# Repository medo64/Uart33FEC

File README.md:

[UART 3.3V Framework Expansion Card](https://medo64.com/uart33fec/)
===================================================================

This Framework laptop expansion card will show up on your system as a serial
device and allow for a non-isolated serial UART communication up to 1 Mbaud
baud rate.

Please note that this card is not using RS-232 but 3.3V TTL.

## UART Pinout

To connect to this board, one has to use a 4-pin JST XH connector. The following
table represents the pinout, pin 1 being on the left as looking into the
expansion card.

| # | Ref | Description                     |
|--:|:---:|---------------------------------|
| 2 | GND | Ground connection               |
| 1 | RXD | Receive (3.3V TTL)              |
| 3 | TXD | Transmit (3.3V TTL)             |
| 4 | 3V3 | 3.3V 400mA (typical) output     |

Using 22 AWG wire 0.25 mm² is recommended.

## Supported Speeds

This board employs the FT232R as its UART chip, and consequently, it supports
all the baud rates this chip [can handle](https://ftdichip.com/Documents/AppNotes/AN232B-05_BaudRates.pdf).
The table below lists the standard baud rates.

| Baud rate |    Actual | Error |    Divisor |
|----------:|----------:|------:|-----------:|
|       300 |       300 | 0.00% |  10000.000 |
|       600 |       600 | 0.00% |   5000.000 |
|     1,200 |     1,200 | 0.00% |   2500.000 |
|     1,800 |     1,800 | 0.00% |   1666.625 |
|     2,400 |     2,400 | 0.00% |   1250.000 |
|     4,800 |     4,800 | 0.00% |    625.000 |
|     7,200 |     7,201 | 0.01% |    416.625 |
|     9,600 |     9,600 | 0.00% |    312.500 |
|    14,400 |    14,406 | 0.04% |    208.250 |
|    19,200 |    19,200 | 0.00% |    156.250 |
|    28,800 |    28,812 | 0.04% |    104.125 |
|    38,400 |    38,400 | 0.00% |     78.125 |
|    57,600 |    57,692 | 0.16% |     52.000 |
|   115,200 |   115,385 | 0.16% |     26.000 |
|   230,400 |   230,769 | 0.16% |     13.000 |
|   460,800 |   461,538 | 0.16% |      6.500 |
|   921,600 |   923,077 | 0.16% |      3.250 |
| 1,000,000 | 1,000,000 | 0.00% |      3.000 |

While chip does support baud rates up to 3 Mbaud, granularity of such rates
is severely limited.

---
*You can check my blog and other projects at [www.medo64.com](https://www.medo64.com/electronics/).*

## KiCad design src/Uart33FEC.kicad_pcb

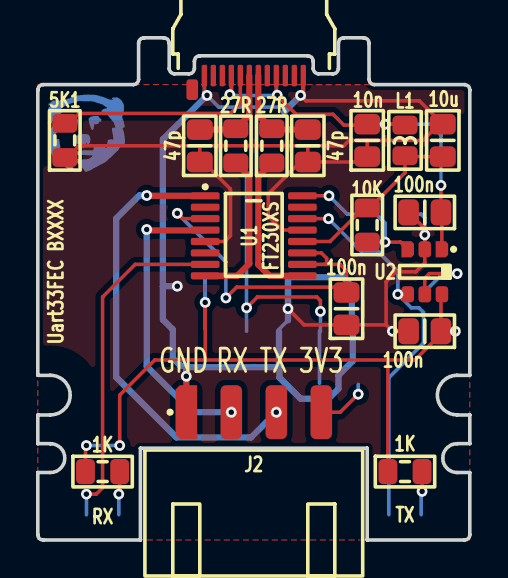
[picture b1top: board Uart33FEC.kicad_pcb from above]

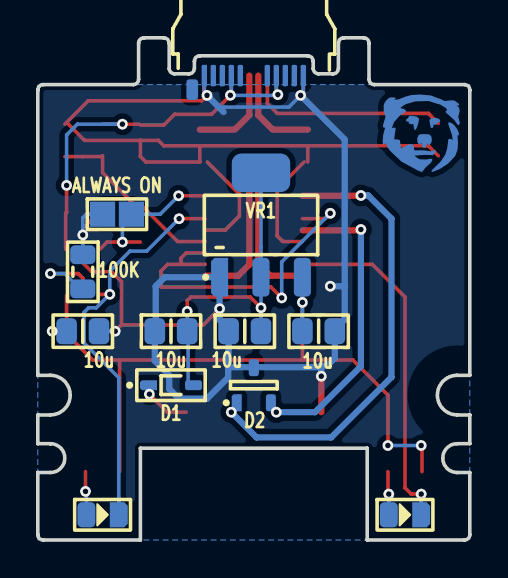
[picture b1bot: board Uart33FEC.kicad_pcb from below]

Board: 2 copper layers, 24.0 x 27.9 mm, 30 parts (12 on the bottom side), 20 nets.

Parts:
C1, C2: 47p; C (0805)
C3: 10n; C (0805)
C4, C5, C6: 100n; C (0805)
C7, C8, C9, C10, C11: 10u; C (0805)
D1: CUS08F30; D (SOD323)
D2: SM05T1G; D TVS 3.3V [D1213A-02SOL-7] (SOT23-3)
DS1: RX; DS (0805)
DS2: TX; DS (0805)
ICON: Medo64; ICON Medo64
J1: 105444-0001; J USB C 3.2 Edge (24w)
J2: B4B-XH-A; J JST XH Edge [UART] (4w)
JP1: ALWAYS ON; JP (0805)
L1: 600R; L (0805)
R1, R2: 27R; R (0805)
R3, R4: 1K; R (0805)
R5: 5K1; R (0805)
R6: 10K; R (0805)
R7: 100K; R (0805)
U1: FT230XS; U Transceiver UART [FT230XS] (SSOP-16)
U2: AP22652; U LoadSwitch Adjustable [AP22652W6-7] (SOT23-6)
VR1: AZ1117IH; VR Linear 3.3V 1000mA [AZ1117IH-3.3TRG1] (SOT223)

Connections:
3V3: C4.2, U1.3, U1.10, U1.11
3V3_OUT: D1.1, J2.4
3V3_SWITCHED: C10.1, C11.1, D1.2, VR1.2
5V: C7.2, L1.1, R6.1, U1.12
5V_SWITCHED: C6.1, C8.1, C9.1, R3.1, R4.1, U2.6, VR1.3
5V_USB: C3.2, C5.1, J1.A4, J1.A9, J1.B04, J1.B09, L1.2, U2.1
GND: C1.1, C2.1, C3.1, C4.1, C5.2, C6.2, C7.1, C8.2, C9.2, C10.2, C11.2, D2.3, J1.A1, J1.A12, J1.B01, J1.B12, J2.1, JP1.2, R5.1, R7.2, U1.5, U1.13, U2.2, VR1.1
ILIM: R7.1, U2.5
LED_RX: DS1.1, U1.7
LED_RX': DS1.2, R3.2
LED_TX: DS2.1, U1.14, U2.4
LED_TX': DS2.2, R4.2
PWREN#: JP1.1, R6.2, U1.16, U2.3
RX: D2.2, J2.2, U1.4
TX: D2.1, J2.3, U1.1
USB_CC: J1.A5, R5.2
USB_DM: C2.2, J1.A7, R2.2
USB_DM': R2.1, U1.9
USB_DP: C1.2, J1.A6, R1.2
USB_DP': R1.1, U1.8

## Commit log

2024-05-11 Updated type-C connector to allow for more soldermask
2024-06-02 Fixed max power
2024-06-02 Changed pinout to GND RXD TXD 3V3
2024-06-02 Changed load switch (400mA limit)
2024-06-06 Refactored output handling
2024-06-10 Connected 3V3 output lines
